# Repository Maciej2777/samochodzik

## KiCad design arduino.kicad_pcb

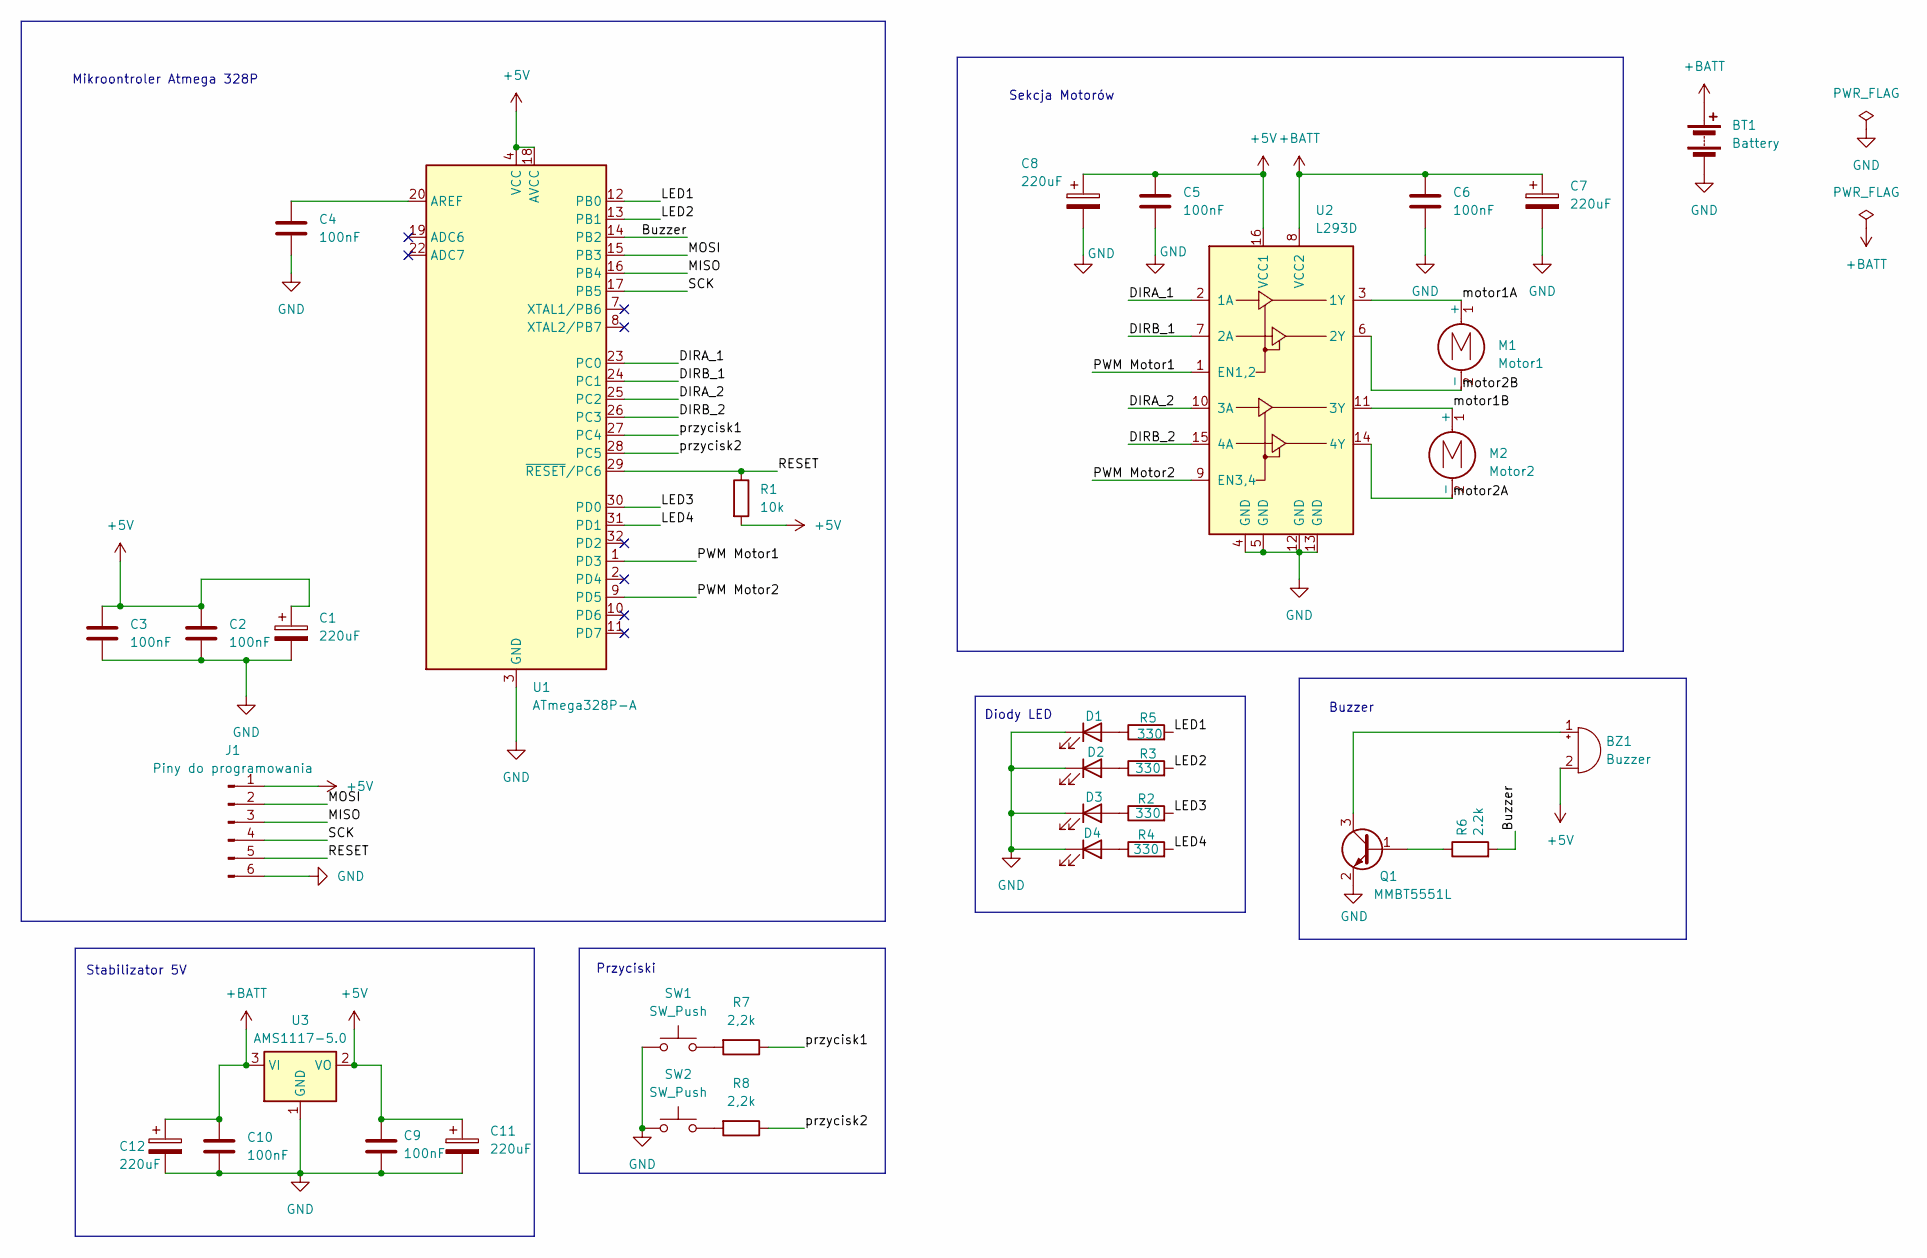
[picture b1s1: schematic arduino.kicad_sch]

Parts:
BT1: Battery; BatteryHolder_MPD_BC2AAPC_2xAA
BZ1: Buzzer; Buzzer_12x9.5RM7.6
C1: 220uF; CP_Radial_D8.0mm_P2.50mm
C2, C3, C4, C5, C6, C9, C10: 100nF; C_0805_2012Metric_Pad1.18x1.45mm_HandSolder
C7, C8, C11, C12: 220uF; CP_Radial_D8.0mm_P5.00mm
D1, D2: LED; LED_D5.0mm
D3, D4: LED; LED_1206_3216Metric_Pad1.42x1.75mm_HandSolder
J1: Piny do programowania; PinHeader_1x06_P2.54mm_Vertical
M1: Motor1; PinHeader_1x02_P2.54mm_Vertical
M2: Motor2; PinHeader_1x02_P2.54mm_Vertical
Q1: MMBT5551L; SOT-23
R1: 10k; R_0805_2012Metric_Pad1.20x1.40mm_HandSolder
R2, R3, R4, R5: 330; R_0805_2012Metric_Pad1.20x1.40mm_HandSolder
R6: 2.2k; R_0805_2012Metric_Pad1.20x1.40mm_HandSolder
R7, R8: 2,2k; R_0805_2012Metric_Pad1.20x1.40mm_HandSolder
SW1, SW2: SW_Push; SW_SPST_EVQQ2
U1: ATmega328P-A; TQFP-32_7x7mm_P0.8mm
U2: L293D; DIP-16_W7.62mm
U3: AMS1117-5.0; SOT-223-3_TabPin2

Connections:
+5V: BZ1.2 (-), C1.1, C2.1, C3.1, C5.1, C8.1, C9.1, C11.1, J1.1, R1.2, U1.4 (VCC), U1.6 (VCC), U1.18 (AVCC), U2.16 (VCC1), U3.2 (VO)
+BATT: BT1.1 (+), C6.1, C7.1, C10.1, C12.1, U2.8 (VCC2), U3.3 (VI)
/Buzzer: R6.2, U1.14 (PB2)
/DIRA_1: U1.23 (PC0), U2.2 (1A)
/DIRA_2: U1.25 (PC2), U2.10 (3A)
/DIRB_1: U1.24 (PC1), U2.7 (2A)
/DIRB_2: U1.26 (PC3), U2.15 (4A)
/LED1: R5.2, U1.12 (PB0)
/LED2: R3.2, U1.13 (PB1)
/LED3: R2.2, U1.30 (PD0)
/LED4: R4.2, U1.31 (PD1)
/MISO: J1.3, U1.16 (PB4)
/MOSI: J1.2, U1.15 (PB3)
/PWM Motor1: U1.1 (PD3), U2.1 (EN1,2)
/PWM Motor2: U1.9 (PD5), U2.9 (EN3,4)
/RESET: J1.5, R1.1, U1.29 (~RESET/PC6)
/SCK: J1.4, U1.17 (PB5)
/motor1A: M1.1 (+), U2.3 (1Y)
/motor1B: M2.1 (+), U2.11 (3Y)
/motor2A: M2.2 (-), U2.14 (4Y)
/motor2B: M1.2 (-), U2.6 (2Y)
/przycisk1: R7.1, U1.27 (PC4)
/przycisk2: R8.1, U1.28 (PC5)
GND: BT1.2 (-), C1.2, C2.2, C3.2, C4.2, C5.2, C6.2, C7.2, C8.2, C9.2, C10.2, C11.2, C12.2, D1.1 (K), D2.1 (K), D3.1 (K), D4.1 (K), J1.6, Q1.2 (E), SW1.1, SW2.1, U1.3 (GND), U1.5 (GND), U1.21 (GND), U2.4 (GND), U2.5 (GND), U2.12 (GND), U2.13 (GND), U3.1 (GND)
unnamed: BZ1.1 (+), Q1.3 (C)
unnamed: D1.2 (A), R5.1
unnamed: D2.2 (A), R3.1
unnamed: D3.2 (A), R2.1
unnamed: D4.2 (A), R4.1
unnamed: Q1.1 (B), R6.1
unnamed: R7.2, SW1.2
unnamed: R8.2, SW2.2
unnamed: C4.1, U1.20 (AREF)

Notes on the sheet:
Buzzer
Diody LED
Przyciski
Stabilizator 5V
Sekcja Motorów
Mikroontroler Atmega 328P

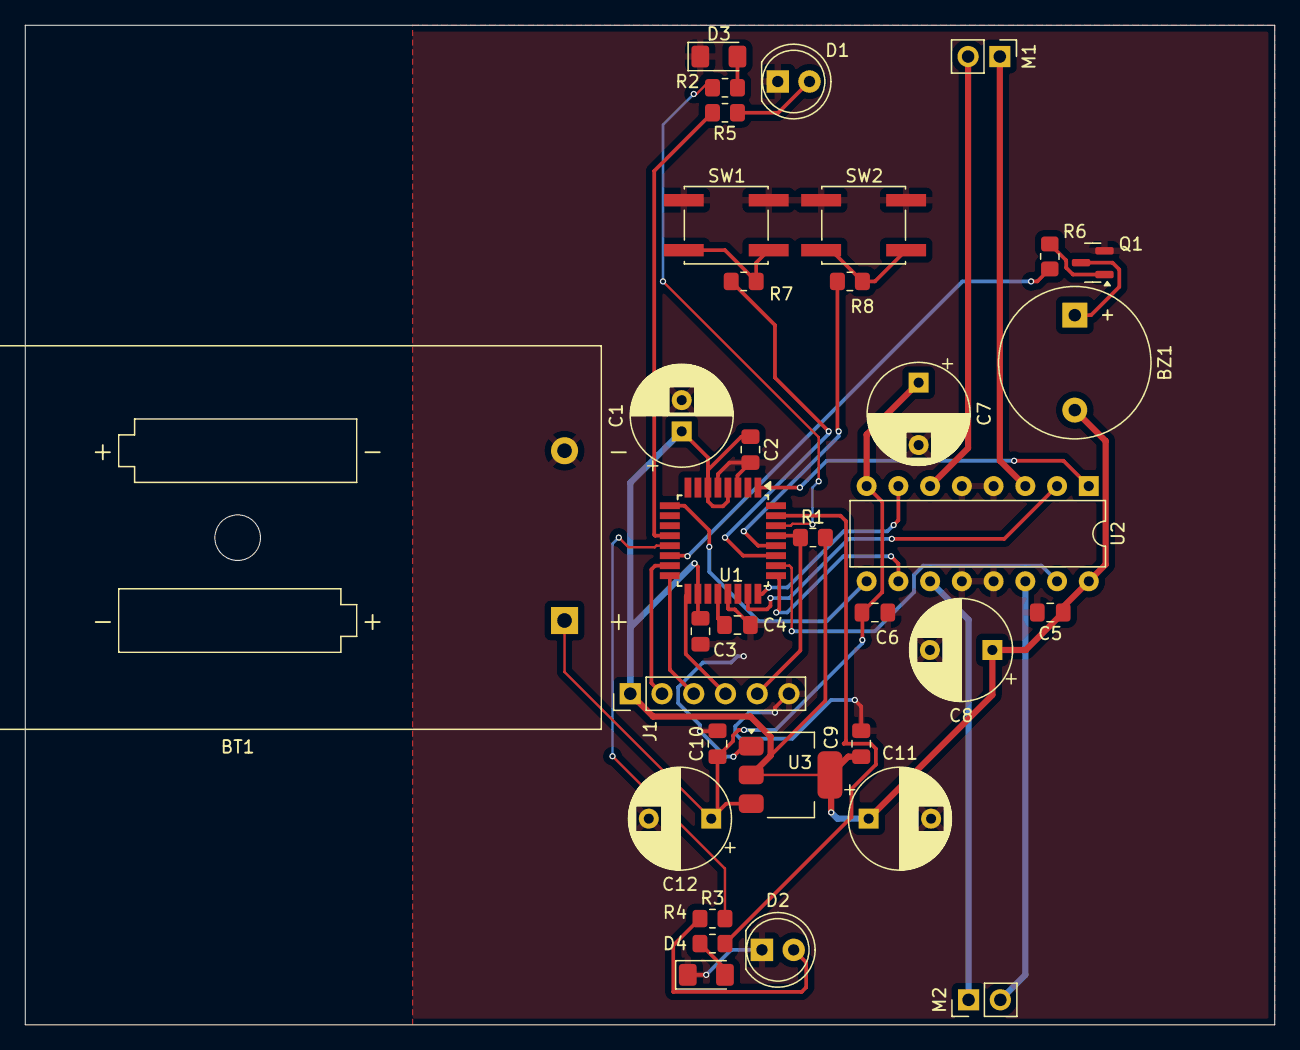
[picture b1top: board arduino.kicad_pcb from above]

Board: 2 copper layers, 100.0 x 80.0 mm, 35 parts (0 on the bottom side), 33 nets.

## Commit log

2024-11-25 dodanie plików kiCad
